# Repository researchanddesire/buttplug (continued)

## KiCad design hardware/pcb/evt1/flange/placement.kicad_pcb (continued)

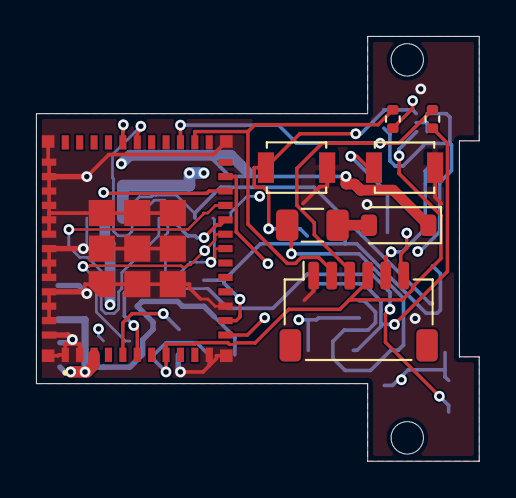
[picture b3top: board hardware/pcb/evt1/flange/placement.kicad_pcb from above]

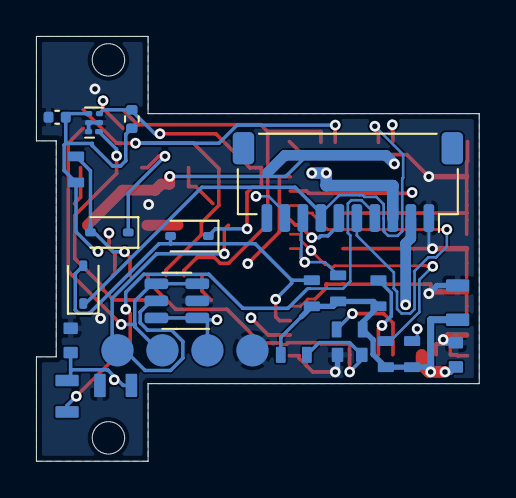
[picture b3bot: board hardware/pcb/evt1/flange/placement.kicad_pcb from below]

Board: 4 copper layers, 24.6 x 23.6 mm, 33 parts (23 on the bottom side), 25 nets.

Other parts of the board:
H1, H2: NPTH_1.8mm_LocatingPin

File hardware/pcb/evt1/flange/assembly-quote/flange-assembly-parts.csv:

Manufacturer,MPN,Quantity_per_board,References,Schematic_value,Footprint,Assembly_note,Manufacturer_source
Diodes Incorporated,B140HW-7,1,D1,Schottky 1A/20V candidate,PrototypeR0:Diodes_B140HW_SOD123_A1_K2,Custom footprint uses logical pad1 ANODE /pad2 CATHODE. Physical cathode stripe goes at the CAD cathode bar/pad2; do not assume generic diode pad1 numbering.,https://www.diodes.com/datasheet/download/B140HW.pdf
Espressif,ESP32-C3-MINI-1-N4X,1,U6,ESP32-C3-MINI-1-N4X candidate,PrototypeR0:Espressif_ESP32-C3-MINI-1_53Pads,Preserve four-layer copper/antenna keepout. Quote stencil/ground-pad process using the native custom53-pad footprint.,https://documentation.espressif.com/esp32-c3-mini-1_datashee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
JST,SM06B-SRSS-TB(LF)(SN),1,J4,SERVICE_USB_BOOT,PrototypeR0:JST_SH_SM06B-SRSS-TB_1x06-1MP_P1.00mm_Horizontal,Board header only. Order matching SHR housings/SSH terminals or qualified precrimp leads separately; flange ends are housed only after feeding free terminals through the neck.,https://www.jst-mfg.com/product/pdf/eng/eSH.pdf
JST,SM10B-SRSS-TB(LF)(SN),1,J7,SM10B-SRSS-TB candidate,PrototypeR0:JST_SH_SM10B-SRSS-TB_1x10-1MP_P1.00mm_Horizontal,Board header only. Order matching SHR housings/SSH terminals or qualified precrimp leads separately; flange ends are housed only after feeding free terminals through the neck.,https://www.jst-mfg.com/product/pdf/eng/eSH.pdf
Littelfuse,1206L050YR,1,F1,PTC 500mA candidate,PrototypeR0:Fuse_1206_3216Metric,"500mA hold PTC, not a precise current limiter. Use6V variant matching this exact part/height, not a taller alternate.",https://www.littelfuse.com/assetdocs/resettable-ptcs-1206l-d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
Murata,GRM155R71C104KA88D,1,C71,100nF,EVT1:C_0402_1005Metric,,https://www.murata.com/en-global/api/pdfdownloadapi?cate=luC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
Murata,GRM188R71C104KA01D,2,C32 C34,100nF,PrototypeR0:Murata_GRM18_0603_Reflow,,https://www.murata.com/en-global/api/pdfdownloadapi?cate=luC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
Murata,GRM21BR61A106KE19L,1,C31,10uF 10V,PrototypeR0:Murata_GRM21_0805_Reflow,,https://www.murata.com/en-global/api/pdfdownloadapi?cate=luC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
Omron,B3U-1000P,2,SW1 SW2,MODE / momentary; POWER / momentary,PrototypeR0:SW_SPST_B3U-1000P,,https://omronfs.omron.com/en_US/ecb/products/pdf/en-b3u.pdf
STMicroelectronics,USBLC6-2SC6,1,U75,USBLC6-2SC6,EVT1:SOT-23-6,,https://www.st.com/resource/en/datasheet/usblc6-2.pdf
TDK,C1608X7R1E105K080AB,1,C33,1uF,PrototypeR0:TDK_C1608_0603_Reflow,,https://product.tdk.com/en/search/capacitor/ceramic/mlcc/inf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
Texas Instruments,TPS3422EGDRYR,1,U71,TPS3422EGDRYR,EVT1:Texas_USON-6_1x1.45mm_P0.5mm_SMD,,https://www.ti.com/lit/ds/symlink/tps3422.pdf
Vishay,BAT54WS-E3-08,3,D71 D72 D73,BAT54WS-E3-08,EVT1:D_SOD-323,,https://www.vishay.com/docs/86465/bat54ws.pdf
Vishay,TNPW040210K0BEED,1,R71,10k,EVT1:R_0402_1005Metric,,https://www.vishay.com/docs/28758/tnpw_e3.pdf
Vishay,TNPW040222R0BEED,2,R75 R76,22R,EVT1:R_0402_1005Metric,,https://www.vishay.com/docs/28758/tnpw_e3.pdf
Vishay,TNPW060310K0BEEA,6,R31 R32 R33 R34 R35 R36,10k,PrototypeR0:Vishay_TNPW0603_IEC_Reflow,,https://www.vishay.com/docs/28758/tnpw_e3.pdf
Vishay,TNPW06034K70BEEA,2,R37 R38,4.7k,PrototypeR0:Vishay_TNPW0603_IEC_Reflow,,https://www.vishay.com/docs/28758/tnpw_e3.pdf
Vishay,TNPW08051M00BEEA,2,R39 R40,1.00M 1%,PrototypeR0:Vishay_TNPW0805_IEC_Reflow,,https://www.vishay.com/docs/28758/tnpw_e3.pdf

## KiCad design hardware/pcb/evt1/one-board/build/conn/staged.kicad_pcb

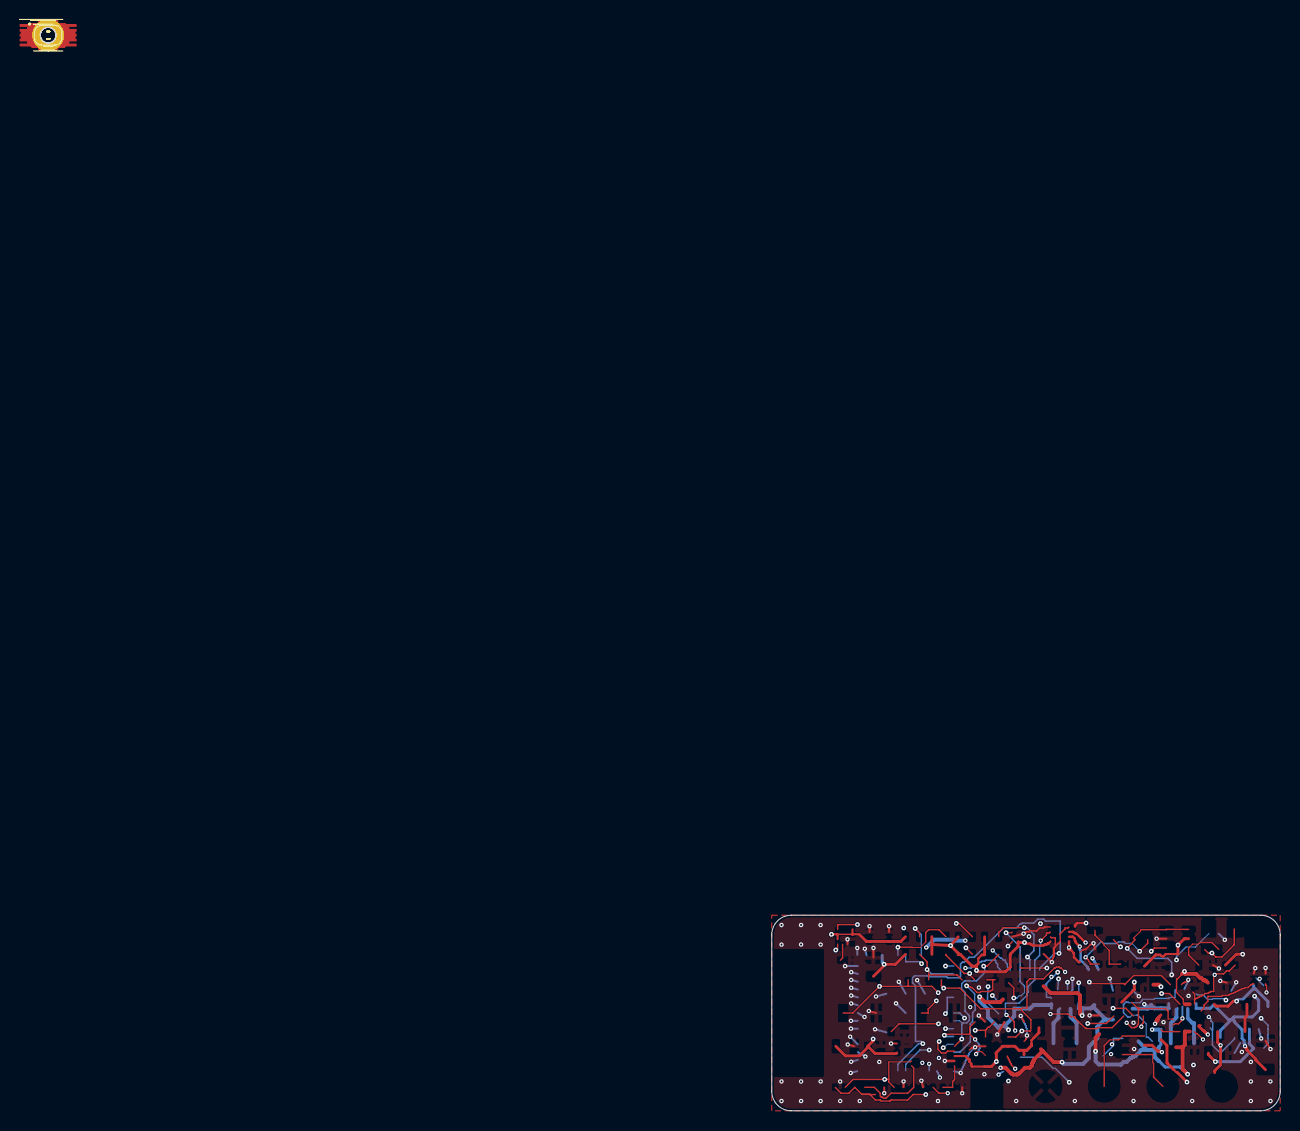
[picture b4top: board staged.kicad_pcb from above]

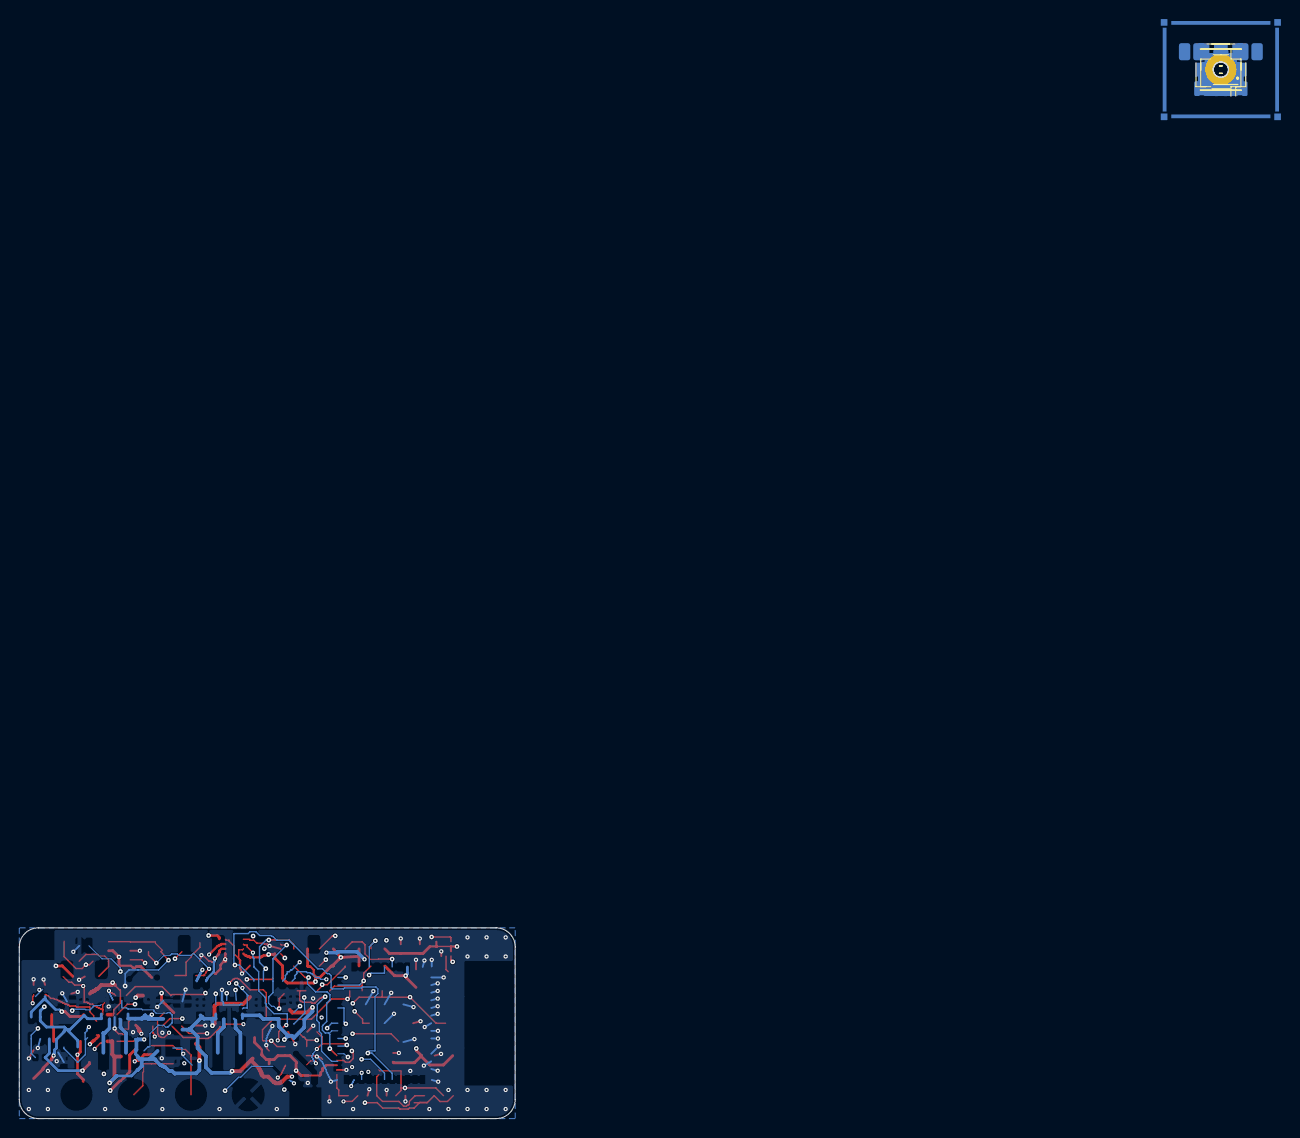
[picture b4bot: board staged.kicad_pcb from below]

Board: 4 copper layers, 52.0 x 20.0 mm, 109 parts (27 on the bottom side), 54 nets.

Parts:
C1, C2, C3: 4.7uF 16V X7R; Murata_GRM21_0805_Reflow
C11, C12, C21, C22, C31: 10uF 10V; Murata_GRM21_0805_Reflow
C13, C14, C15, C23, C24, C25: 22uF 10V X7R; Murata_GRM31_1206_Reflow
C16, C26: 100nF 10V; Murata_GRM18_0603_Reflow
C27, C32, C34, C43, C44: 100nF; Murata_GRM18_0603_Reflow
C28, C29, C61, C71, C82: 100nF; C_0402_1005Metric
C30: 47uF 10V; Murata_GRM32_1210_Reflow
C33: 1uF; TDK_C1608_0603_Reflow
C51, C52, C53, C54: 10uF 10V X5R 0603 HF; TDK_C1608_0603_Reflow
C62, C63: 10nF; C_0402_1005Metric
C81: 220nF; C_0402_1005Metric
C83: 47uF 10V / Ceff>=10uF at3V3; C_0805_2012Metric
C84: 100nF / VDDIO local; C_0402_1005Metric
C88: 10nF 50V X7R; C_0402_1005Metric
CT1, CT2, CT3, CT4: 1946-0-00-15-00-00-03-0; MillMax_1946_0_PTH_Study
D1: Schottky 1A/20V candidate; Diodes_B140HW_SOD123_A1_K2
D71, D72, D73: BAT54WS-E3-08; D_SOD-323
F1: PTC 500mA candidate; Fuse_1206_3216Metric
J2: BATTERY 3P JST SH; JST_SH_SM03B-SRSS-TB_1x03-1MP_P1.00mm_Horizontal
J3: MOTOR_2PIN; JST_SH_SM02B-SRSS-TB_1x02-1MP_P1.00mm_Horizontal
J4: SERVICE_USB_BOOT; JST_SH_SM06B-SRSS-TB_1x06-1MP_P1.00mm_Horizontal
J5: TIP NTC / GND; JST_SH_BM02B-SRSS-TB_1x02-1MP_P1.00mm_Vertical
JP1: CHARGE_PERMISSION / OPEN; SolderJumper-2_P1.3mm_Open_RoundedPad1.0x1.5mm
L1, L2: 1.5uH / Isat>=4A candidate; L_Coilcraft_XxL4020
MH1, MH3: PROVISIONAL M1.4 support
Q1: AO3400A; SOT-23
R1: 8.87k 1% / ~100mA; R_0402_1005Metric
R2: 3.24k 1%; R_0402_1005Metric
R3, R4, R5, R71: 10k; R_0402_1005Metric
R11: 312k 0.1%; Vishay_TNPW0603_IEC_Reflow
R12, R22: 100k 0.1%; Vishay_TNPW0603_IEC_Reflow
R13, R26, R31, R32, R33, R34, R35, R36: 10k; Vishay_TNPW0603_IEC_Reflow
R21: 360k 0.1%; RESI_PTFR0805_C16003
R23, R24, R25: 100k; R_0402_1005Metric
R37, R38: 4.7k; Vishay_TNPW0603_IEC_Reflow
R39, R40: 1.00M 1%; Vishay_TNPW0805_IEC_Reflow
R42: 470k 1%; R_0402_1005Metric
R43: 715k 0.1%; RESI_PTFR0805_C16003
R44: 110k 0.1%; Vishay_TNPW0603_IEC_Reflow
R45: 200k 0.1%; Vishay_TNPW0603_IEC_Reflow
R46: 11k 1%; R_0402_1005Metric
R47: 1k 1%; R_0402_1005Metric
R48: 100k 1%; R_0402_1005Metric
R61, R62, R63, R88: 10k 0.1%; R_0402_1005Metric
R75, R76: 22R; R_0402_1005Metric
SW1: POWER / momentary; SW_SPST_B3U-1000P
SW2: MODE / momentary; SW_SPST_B3U-1000P
U1: BQ24074RGT candidate; TI_RGT0016C_3x3mm_BQ24074_EP1.68mm
U2, U3: TPS63070RNM candidate; TI_RNM0015A_2.5x3mm_TPS63070
U4: SN74LVC1G11DBV candidate; SOT-23-6
U5: DRV8212DSG candidate; WSON-8-1EP_2x2mm_P0.5mm_EP0.9x1.6mm
U6: ESP32-C3-MINI-1-H4X; Espressif_ESP32-C3-MINI-1_53Pads
U7: ADS1115IDGSR /0x48; VSSOP-10_3x3mm_P0.5mm
U8: TPS3700DDCR; TSOT-23-6
U9: TPS3808G33QDBVRQ1; SOT-23-6
U71: TPS3422EGDRYR; Texas_USON-6_1x1.45mm_P0.5mm_SMD
U75: USBLC6-2SC6; SOT-23-6
U81: LSM303AGRTR; LGA-12_2x2mm_P0.5mm

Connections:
3V3: C13.1, C14.1, C15.1, C27.1, C29.1, C31.1, C32.1, C43.1, C52.1, C61.1, C71.1, C82.1, C83.1, C84.1, R4.1, R5.1, R11.1, R31.1, R32.1, R33.1, R34.1, R35.1, R36.1, R37.1, R38.1, R42.1, R71.1, U2.7, U2.8, U4.5, U5.8, U6.3, U7.8, U8.5, U9.5, U71.4, U81.2, U81.3, U81.9, U81.10
BOOT_N: D73.2, J4.5, R34.2, U6.23
CHARGE_CE_N: Q1.3, R3.2, U1.4
CHARGE_GATE: Q1.1, R47.2, R48.1
CHARGE_PERMIT: JP1.2, R47.1
CHARGE_STATUS_N: R5.2, U1.9
CHARGE_TEMP_OK: JP1.1, R46.2, U8.1, U8.6, U9.1
CHG_ILIM: R2.1, U1.12
CHG_ISET: R1.1, U1.16
DOCK_5V: CT4.1, F1.1, U75.5
DOCK_FUSED: D1.1, F1.2
DOCK_PRESENT_N: D72.1, R4.2, U1.7, U4.6, U6.30
GND: C1.2, C2.2, C3.2, C11.2, C12.2, C13.2, C14.2, C15.2, C16.2, C21.2, C22.2, C23.2, C24.2, C25.2, C26.2, C27.2, C28.2, C29.2, C30.2, C31.2, C32.2, C33.2, C34.2, C43.2, C44.2, C51.2, C52.2, C53.2, C54.2, C61.2, C62.2, C63.2, C71.2, C81.2, C82.2, C83.2, C84.2, C88.2, CT1.1, J2.2, J4.1, J5.2, Q1.2, R1.2, R2.2, R12.2, R22.2, R23.2, R24.2, R25.2, R40.2, R45.2, R48.2, R63.2, SW1.2, SW2.2, U1.5, U1.6, U1.8, U1.17, U2.4, U2.10, U2.15, U3.4, U3.10, U3.15, U4.2, U5.4, U5.5, U5.7, U5.9, U6.1, U6.2, U6.11, U6.14, U6.36, U6.37, U6.38, U6.39, U6.40, U6.41, U6.42, U6.43, U6.44, U6.45, U6.46, U6.47, U6.48, U6.49, U6.50, U6.51, U6.52, U6.53, U7.1, U7.3, U7.7, U8.2, U9.2, U71.2, U71.5, U71.6, U75.2, U81.6, U81.8
I2C_SCL: R38.2, U6.19, U7.10, U81.1
I2C_SDA: R37.2, U6.18, U7.9, U81.4
MAG_C1: C81.1, U81.5
MCU_EN: C33.1, J4.4, R31.2, U6.8, U71.1
MODE_N: D73.1, R36.2, SW2.1, U6.6
MOTOR_3V7: C23.1, C24.1, C25.1, C28.1, C30.1, C54.1, R21.1, U3.7, U3.8, U5.1
MOTOR_ARM: R23.1, U3.14, U4.3, U6.21
MOTOR_IN1: R25.1, U4.4, U5.6
MOTOR_N: J3.2, U5.3
MOTOR_P: J3.1, U5.2
MOTOR_PWM: R24.1, U4.1, U6.20
PACK_MON_NTC: C88.1, R88.2, U7.6
PACK_NTC: J2.3, R42.2, R88.1, U1.1
PACK_P: C2.1, J2.1, R39.1, U1.2, U1.3
POWER_N: D71.2, D72.2, R35.2, U6.13
POWER_SWITCH_N: D71.1, R71.2, SW1.1, U71.3
REG1_AUX: C16.1, U2.3
REG1_FB: R11.2, R12.1, U2.5
REG1_L1: L1.1, U2.11
REG1_L2: L1.2, U2.9
REG1_PS: R13.2, U2.1, U2.14
REG2_AUX: C26.1, U3.3
REG2_FB: R21.2, R22.1, U3.5
REG2_L1: L2.1, U3.11
REG2_L2: L2.2, U3.9
REG2_PS: R26.2, U3.1
STRAP2: R32.2, U6.5
STRAP8: R33.2, U6.22
SYS: C3.1, C11.1, C12.1, C21.1, C22.1, C51.1, C53.1, R13.1, R26.1, U1.10, U1.11, U2.12, U2.13, U3.12, U3.13
TEMP_COLD_IN: R44.2, R45.1, U8.4
TEMP_HOT_IN: R43.2, R44.1, U8.3
TIP_EXC_EN: R61.1, R62.1, U6.16
TIP_EXC_HALF: C63.1, R62.2, R63.1, U7.5
TIP_NTC: C62.1, J5.1, R61.2, U7.4
UART_TX: J4.6, U6.31
USB_DM: J4.2, R75.2, U6.26
USB_DM_CONTACT: CT2.1, R75.1, U75.1, U75.6
USB_DP: J4.3, R76.2, U6.27
USB_DP_CONTACT: CT3.1, R76.1, U75.3, U75.4
VBAT_ADC: C34.1, R39.2, R40.1, U6.12
VBUS_CHG: C1.1, C44.1, D1.2, R3.1, R46.1, U1.13, U9.3, U9.6

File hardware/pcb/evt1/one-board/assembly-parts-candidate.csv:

Comment,Designator,Footprint,Manufacturer Part Number,Baseline MPN
4.7uF 16V X7R,C1,Murata_GRM21_0805_Reflow,GRM21BR71C475KE51L,GRM21BR71A475KA73L
4.7uF 16V X7R,C2,Murata_GRM21_0805_Reflow,GRM21BR71C475KE51L,GRM21BR71A475KA73L
4.7uF 16V X7R,C3,Murata_GRM21_0805_Reflow,GRM21BR71C475KE51L,GRM21BR61A106KE19L
10uF 10V,C11,Murata_GRM21_0805_Reflow,GRM21BR61A106KE19L,GRM21BR61A106KE19L
22uF 10V X7R,C13,Murata_GRM31_1206_Reflow,GRM31CR71A226KE15L,GRM31CR71A226KE15L
22uF 10V X7R,C14,Murata_GRM31_1206_Reflow,GRM31CR71A226KE15L,GRM31CR71A226KE15L
22uF 10V X7R,C15,Murata_GRM31_1206_Reflow,GRM31CR71A226KE15L,GRM31CR71A226KE15L
100nF 10V,C16,Murata_GRM18_0603_Reflow,GRM188R71C104KA01D,GRM188R71C104KA01D
10uF 10V X5R 0603 HF,C51,TDK_C1608_0603_Reflow,CL10A106KP8NNNC,C1608X5R1A106K080AC
10uF 10V X5R 0603 HF,C52,TDK_C1608_0603_Reflow,CL10A106KP8NNNC,C1608X5R1A106K080AC
1.5uH / Isat>=4A candidate,L1,L_Coilcraft_XxL4020,XFL4020-152MEC,XFL4020-152MEC
8.87k 1% / ~100mA,R1,R_0402_1005Metric,TC0210B8871TCC,TNPW04028K87BEED
3.24k 1%,R2,R_0402_1005Metric,RT0402BRD073K24L,TNPW04023K24BEED
10k,R3,R_0402_1005Metric,TNPW040210K0BEED,TNPW040210K0BEED
10k,R4,R_0402_1005Metric,TNPW040210K0BEED,TNPW040210K0BEED
10k,R5,R_0402_1005Metric,TNPW040210K0BEED,TNPW040210K0BEED
312k 0.1%,R11,Vishay_TNPW0603_IEC_Reflow,RT0603BRD07312KL,TNPW0603312KBEEA
100k 0.1%,R12,Vishay_TNPW0603_IEC_Reflow,TNPW0603100KBEEA,TNPW0603100KBEEA
10k,R13,Vishay_TNPW0603_IEC_Reflow,TNPW060310K0BEEA,TNPW060310K0BEEA
BQ24074RGT candidate,U1,TI_RGT0016C_3x3mm_BQ24074_EP1.68mm,BQ24074RGTR,BQ24074RGTR
TPS63070RNM candidate,U2,TI_RNM0015A_2.5x3mm_TPS63070,TPS63070RNMR,TPS63070RNMR
10uF 10V,C31,Murata_GRM21_0805_Reflow,GRM21BR61A106KE19L,GRM21BR61A106KE19L
100nF,C32,Murata_GRM18_0603_Reflow,GRM188R71C104KA01D,GRM188R71C104KA01D
1uF,C33,TDK_C1608_0603_Reflow,CGA3E1X7R1V105KT000N,C1608X7R1E105K080AB
100nF,C34,Murata_GRM18_0603_Reflow,GRM188R71C104KA01D,GRM188R71C104KA01D
SERVICE_USB_BOOT,J4,JST_SH_SM06B-SRSS-TB_1x06-1MP_P1.00mm_Horizontal,SM06B-SRSS-TB(LF)(SN),SM06B-SRSS-TB(LF)(SN)
10k,R31,Vishay_TNPW0603_IEC_Reflow,TNPW060310K0BEEA,TNPW060310K0BEEA
10k,R32,Vishay_TNPW0603_IEC_Reflow,TNPW060310K0BEEA,TNPW060310K0BEEA
10k,R33,Vishay_TNPW0603_IEC_Reflow,TNPW060310K0BEEA,TNPW060310K0BEEA
10k,R34,Vishay_TNPW0603_IEC_Reflow,TNPW060310K0BEEA,TNPW060310K0BEEA
10k,R35,Vishay_TNPW0603_IEC_Reflow,TNPW060310K0BEEA,TNPW060310K0BEEA
10k,R36,Vishay_TNPW0603_IEC_Reflow,TNPW060310K0BEEA,TNPW060310K0BEEA
4.7k,R37,Vishay_TNPW0603_IEC_Reflow,TNPW06034K70BEEA,TNPW06034K70BEEA
4.7k,R38,Vishay_TNPW0603_IEC_Reflow,TNPW06034K70BEEA,TNPW06034K70BEEA
1.00M 1%,R39,Vishay_TNPW0805_IEC_Reflow,TNPW08051M00BEEA,TNPW08051M00BEEA
1.00M 1%,R40,Vishay_TNPW0805_IEC_Reflow,TNPW08051M00BEEA,TNPW08051M00BEEA
POWER / momentary,SW1,SW_SPST_B3U-1000P,B3U-1000P,B3U-1000P
MODE / momentary,SW2,SW_SPST_B3U-1000P,B3U-1000P,B3U-1000P
ESP32-C3-MINI-1-H4X,U6,Espressif_ESP32-C3-MINI-1_53Pads,ESP32-C3-MINI-1-H4X,ESP32-C3-MINI-1-N4X
100nF,C43,Murata_GRM18_0603_Reflow,GRM188R71C104KA01D,GRM188R71C104KA01D
100nF,C44,Murata_GRM18_0603_Reflow,GRM188R71C104KA01D,GRM188R71C104KA01D
AO3400A,Q1,SOT-23,AO3400A,AO3400A
10.0k 0.1%,R42,R_0402_1005Metric,TNPW040210K0BEED,TNPW040210K0BEED
715k 0.1%,R43,RESI_PTFR0805_C16003,PTFR0805B715KP9,TNPW0805715KBEEA
110k 0.1%,R44,Vishay_TNPW0603_IEC_Reflow,TNPW0603110KBEEA,TNPW0603110KBEEA
200k 0.1%,R45,Vishay_TNPW0603_IEC_Reflow,ERA3AEB204V,TNPW0603200KBEEA
11k 1%,R46,R_0402_1005Metric,RT0402BRD0711KL,TNPW040211K0BEED
1k 1%,R47,R_0402_1005Metric,TNPW04021K00BEED,TNPW04021K00BEED
100k 1%,R48,R_0402_1005Metric,TNPW0402100KBEED,TNPW0402100KBEED
TPS3700DDCR,U8,TSOT-23-6,TPS3700DDCR,TPS3700DDCR
TPS3808G33QDBVRQ1,U9,SOT-23-6,TPS3808G33QDBVRQ1,TPS3808G33DBVR
100nF,C71,C_0402_1005Metric,GRM155R71C104KA88D,GRM155R71C104KA88D
BAT54WS-E3-08,D71,D_SOD-323,BAT54WS-E3-08,BAT54WS-E3-08
BAT54WS-E3-08,D72,D_SOD-323,BAT54WS-E3-08,BAT54WS-E3-08
BAT54WS-E3-08,D73,D_SOD-323,BAT54WS-E3-08,BAT54WS-E3-08
10k,R71,R_0402_1005Metric,TNPW040210K0BEED,TNPW040210K0BEED
TPS3422EGDRYR,U71,Texas_USON-6_1x1.45mm_P0.5mm_SMD,TPS3422EGDRYR,TPS3422EGDRYR
10uF 10V,C21,Murata_GRM21_0805_Reflow,GRM21BR61A106KE19L,GRM21BR61A106KE19L
22uF 10V X7R,C23,Murata_GRM31_1206_Reflow,GRM31CR71A226KE15L,GRM31CR71A226KE15L
22uF 10V X7R,C24,Murata_GRM31_1206_Reflow,GRM31CR71A226KE15L,GRM31CR71A226KE15L
22uF 10V X7R,C25,Murata_GRM31_1206_Reflow,GRM31CR71A226KE15L,GRM31CR71A226KE15L
100nF 10V,C26,Murata_GRM18_0603_Reflow,GRM188R71C104KA01D,GRM188R71C104KA01D
100nF,C27,Murata_GRM18_0603_Reflow,GRM188R71C104KA01D,GRM188R71C104KA01D
100nF,C28,C_0402_1005Metric,GRM155R71C104KA88D,GRM155R71C104KA88D
100nF,C29,C_0402_1005Metric,GRM155R71C104KA88D,GRM155R71C104KA88D
47uF 10V,C30,Murata_GRM32_1210_Reflow,GRM32ER61A476KE20L,GRM32ER61A476KE20L
10uF 10V X5R 0603 HF,C53,TDK_C1608_0603_Reflow,CL10A106KP8NNNC,C1608X5R1A106K080AC
10uF 10V X5R 0603 HF,C54,TDK_C1608_0603_Reflow,CL10A106KP8NNNC,C1608X5R1A106K080AC
MOTOR_2PIN,J3,JST_SH_SM02B-SRSS-TB_1x02-1MP_P1.00mm_Horizontal,SM02B-SRSS-TB(LF)(SN),SM02B-SRSS-TB(LF)(SN)
1.5uH / Isat>=4A candidate,L2,L_Coilcraft_XxL4020,XFL4020-152MEC,XFL4020-152MEC
360k 0.1%,R21,RESI_PTFR0805_C16003,PTFR0805B360KN9,TNPW0805362KBEEA
100k 0.1%,R22,Vishay_TNPW0603_IEC_Reflow,TNPW0603100KBEEA,TNPW0603100KBEEA
100k,R23,R_0402_1005Metric,TNPW0402100KBEED,TNPW0402100KBEED
100k,R24,R_0402_1005Metric,TNPW0402100KBEED,TNPW0402100KBEED
100k,R25,R_0402_1005Metric,TNPW0402100KBEED,TNPW0402100KBEED
10k,R26,Vishay_TNPW0603_IEC_Reflow,TNPW060310K0BEEA,TNPW060310K0BEEA
TPS63070RNM candidate,U3,TI_RNM0015A_2.5x3mm_TPS63070,TPS63070RNMR,TPS63070RNMR
SN74LVC1G11DBV candidate,U4,SOT-23-6,SN74LVC1G11DBVR,SN74LVC1G11DBVR
DRV8212DSG candidate,U5,WSON-8-1EP_2x2mm_P0.5mm_EP0.9x1.6mm,DRV8212DSGR,DRV8212DSGR
100nF,C61,C_0402_1005Metric,GRM155R71C104KA88D,GRM155R71C104KA88D
10nF,C62,C_0402_1005Metric,GRM155R71H103KA88D,GRM155R71H103KA88D
10nF,C63,C_0402_1005Metric,GRM155R71H103KA88D,GRM155R71H103KA88D
10nF 50V X7R,C88,C_0402_1005Metric,GRM155R71H103KA88D,
TIP NTC / GND,J5,JST_SH_BM02B-SRSS-TB_1x02-1MP_P1.00mm_Vertical,BM02B-SRSS-TB(LF)(SN),BM02B-SRSS-TB(LF)(SN)
PACK MONITOR NTC / GND,J8,JST_SH_SM02B-SRSS-TB_1x02-1MP_P1.00mm_Horizontal,SM02B-SRSS-TB(LF)(SN),
10k 0.1%,R61,R_0402_1005Metric,TNPW040210K0BEED,TNPW040210K0BEED
10k 0.1%,R62,R_0402_1005Metric,TNPW040210K0BEED,TNPW040210K0BEED
10k 0.1%,R63,R_0402_1005Metric,TNPW040210K0BEED,TNPW040210K0BEED
10k 0.1%,R88,R_0402_1005Metric,TNPW040210K0BEED,
ADS1115IDGSR /0x48,U7,VSSOP-10_3x3mm_P0.5mm,ADS1115IDGSR,ADS1115IDGSR
Schottky 1A/20V candidate,D1,Diodes_B140HW_SOD123_A1_K2,B140HW-7,B140HW-7
PTC 500mA candidate,F1,Fuse_1206_3216Metric,1206L050YR,1206L050YR
22R,R75,R_0402_1005Metric,RC0402FR-0722RL,TNPW040222R0BEED
22R,R76,R_0402_1005Metric,RC0402FR-0722RL,TNPW040222R0BEED
USBLC6-2SC6,U75,SOT-23-6,USBLC6-2SC6,USBLC6-2SC6
220nF,C81,C_0402_1005Metric,GRM155R71C224KA12D,GRM155R71C224KA12D
100nF,C82,C_0402_1005Metric,GRM155R71C104KA88D,GRM155R71C104KA88D
47uF 10V / Ceff>=10uF at3V3,C83,C_0805_2012Metric,MSASL21GBB5476MTNA01,C2012X5R1E226M125AC
100nF / VDDIO local,C84,C_0402_1005Metric,GRM155R71C104KA88D,GRM155R71C104KA88D
LSM303AGRTR,U81,LGA-12_2x2mm_P0.5mm,LSM303AGRTR,LSM303AGRTR
